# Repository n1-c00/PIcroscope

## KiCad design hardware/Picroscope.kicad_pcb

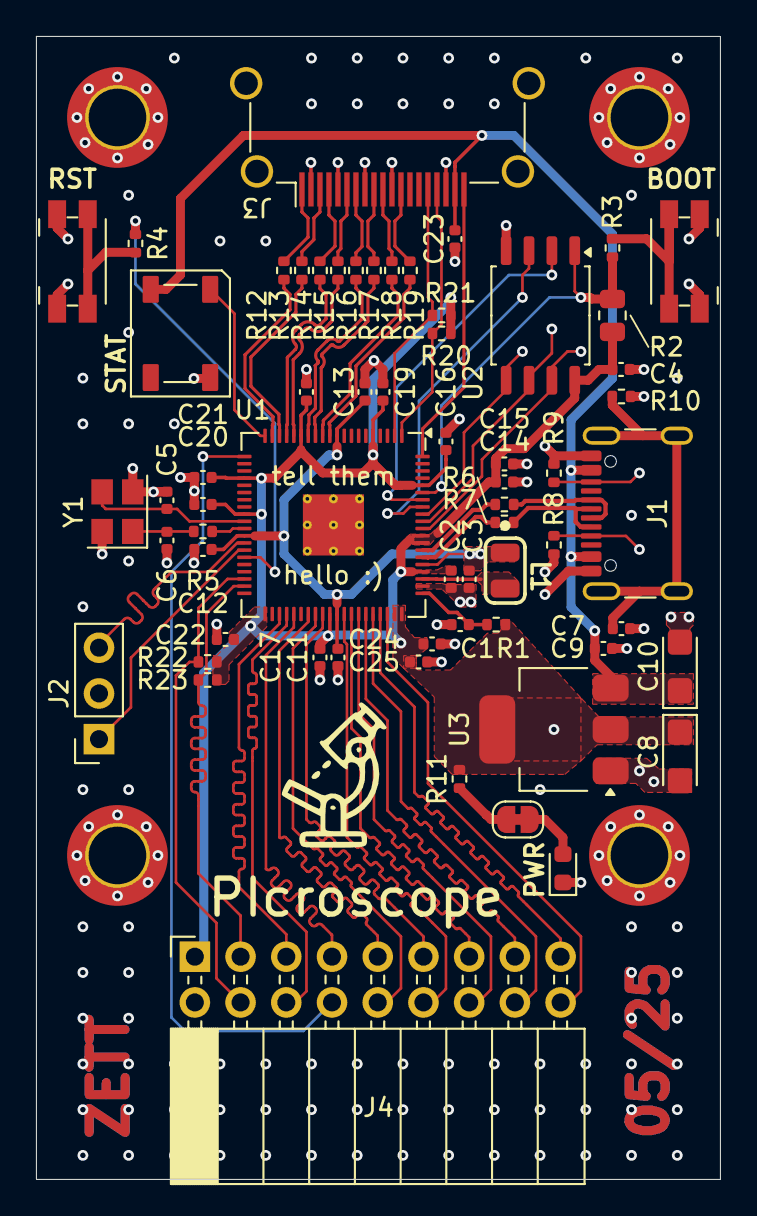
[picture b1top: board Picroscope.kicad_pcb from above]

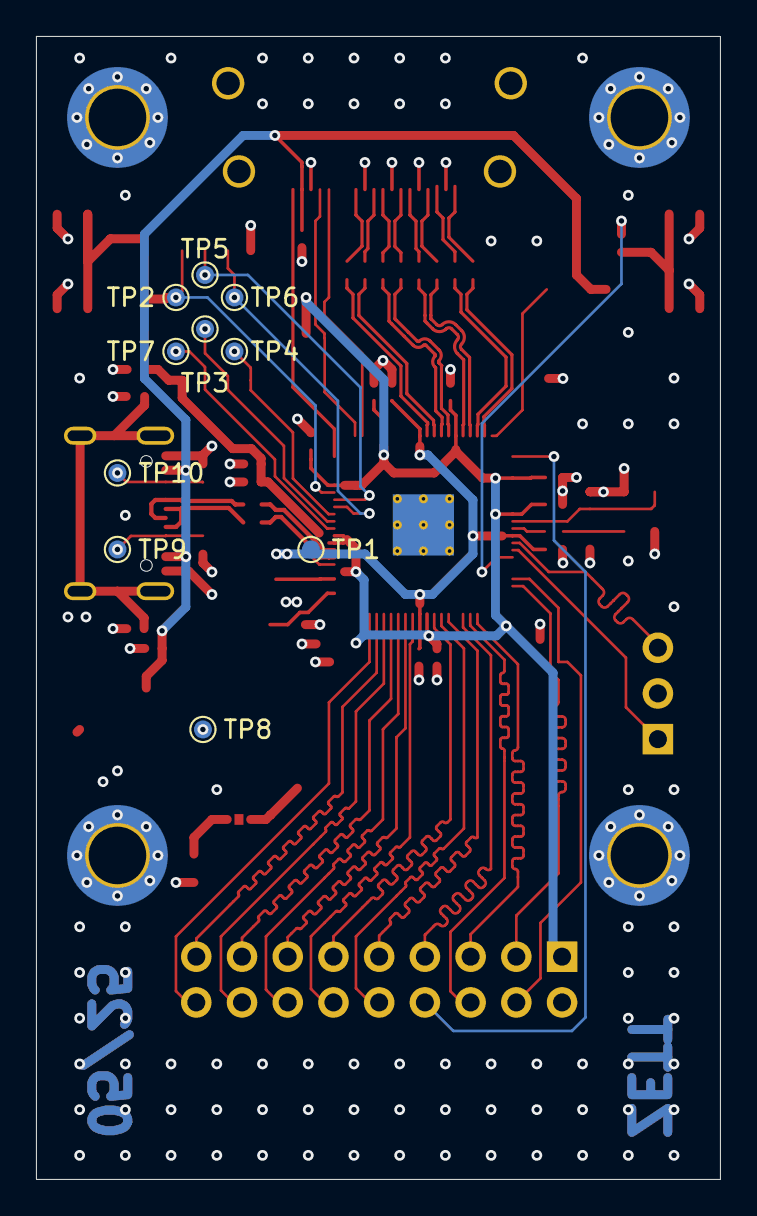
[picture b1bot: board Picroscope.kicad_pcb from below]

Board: 4 copper layers, 38.0 x 63.5 mm, 76 parts (10 on the bottom side), 65 nets.

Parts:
C1, C2, C3: 4.7u; C_0402_1005Metric
C4, C9, C11, C12, C13, C14, C15, C16, C17, C18, C19, C20, C21, C22, C23, C24, C25: 100n; C_0402_1005Metric
C5, C6: 15p; C_0402_1005Metric
C7: 100nF; C_0402_1005Metric
C8, C10: 22uF; CP_EIA-3216-18_Kemet-A
D1: LED; LED_0603_1608Metric
D2: WS2812B-2020; LED_WS2812B_PLCC4_5.0x5.0mm_P3.2mm
H1, H2, H3, H4: MountingHole_Pad; MountingHole_3.2mm_M3_DIN965_Pad_TopBottom
J1: USB_C_Receptacle_USB2.0_16P; USB_C_Receptacle_GCT_USB4105-xx-A_16P_TopMnt_Horizontal
J2: Conn_01x03_Pin; PinSocket_1x03_P2.54mm_Vertical
J3: HDMI_A; HDMI_A_Amphenol_10029449-x01xLF_Horizontal
J4: Conn_02x09_Odd_Even; PinSocket_2x09_P2.54mm_Horizontal
JP1: Jumper_2_Bridged; SolderJumper-2_P1.3mm_Bridged_RoundedPad1.0x1.5mm
L1: 3.3uH; RP235x_Inductor
R1, R6, R7: 27R; R_0402_1005Metric
R2: 1k; R_0805_2012Metric
R3, R4, R5, R11: 1k; R_0402_1005Metric
R8, R9, R10, R20, R21, R22, R23: 5.1k; R_0402_1005Metric
R12, R13, R14, R15, R16, R17, R18, R19: 270R; R_0402_1005Metric
SW1, SW2: SMD_Pushbutton; Panasonic_EVQPUJ_EVQPUA
TP1, TP2, TP3, TP4, TP5, TP6, TP7, TP8, TP9, TP10: TestPoint; TestPoint_Pad_D1.0mm
U1: RP2350B-QFN80; QFN-80-1EP_10x10mm_P0.4mm_EP3.4x3.4mm_ThermalVias
U2: W25Q32JVSS; SOIC-8_5.23x5.23mm_P1.27mm
U3: AMS1117-3.3; SOT-223-3_TabPin2
Y1: ABM8-272-T3; Crystal_SMD_3225-4Pin_3.2x2.5mm

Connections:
+1V1: C3.1, C11.1, C12.1, C13.1, L1.1, TP1.1, U1.10 (DVDD), U1.32 (DVDD), U1.51 (DVDD), U1.65 (VREG_FB)
+3V3: C2.1, C4.1, C8.1, C14.1, C15.1, C16.1, C17.1, C18.1, C19.1, C20.1, C21.1, C22.1, C24.1, C25.1, J4.1, R1.1, R2.1, R11.2, R20.1, R21.1, R22.1, R23.1, TP8.1, U1.5 (IOVDD), U1.15 (IOVDD), U1.24 (IOVDD), U1.29 (IOVDD), U1.41 (IOVDD), U1.50 (IOVDD), U1.59 (ADC_AVDD), U1.60 (IOVDD), U1.64 (VREG_VIN), U1.68 (USB_OTP_VDD), U1.69 (QSPI_IOVDD), U1.76 (IOVDD), U2.8 (VCC), U3.2 (VO)
/CAM_D2: J4.16, U1.56 (GPIO45_ADC5)
/CAM_D3: J4.15, U1.55 (GPIO44_ADC4)
/CAM_D4: J4.14, U1.54 (GPIO43_ADC3)
/CAM_D5: J4.13, U1.53 (GPIO42_ADC2)
/CAM_D6: J4.12, U1.52 (GPIO41_ADC1)
/CAM_D7: J4.11, U1.49 (GPIO40_ADC0)
/CAM_D8: J4.10, U1.48 (GPIO39)
/CAM_D9: J4.9, U1.47 (GPIO38)
/CAM_HSYNC: J4.6, U1.44 (GPIO35)
/CAM_PCLK: J4.7, U1.45 (GPIO36)
/CAM_PWDN: J4.18, U1.58 (GPIO47_ADC7)
/CAM_Reset: J4.17, U1.57 (GPIO46_ADC6)
/CAM_VSYNC: J4.5, U1.43 (GPIO34)
/CLKOUT0: J4.8, U1.21 (GPIO21)
/HDMI_CK+: J3.10 (CK+), R18.2
/HDMI_CK-: J3.12 (CK-), R19.2
/HDMI_D0+: J3.7 (D0+), R16.2
/HDMI_D0-: J3.9 (D0-), R17.2
/HDMI_D1+: J3.4 (D1+), R14.2
/HDMI_D1-: J3.6 (D1-), R15.2
/HDMI_D2+: J3.1 (D2+), R12.2
/HDMI_D2-: J3.3 (D2-), R13.2
/HDMI_HPD: J3.19 (HPD), U1.80 (GPIO3)
/I2C0_SCL: J3.15 (SCL), R21.2, U1.2 (GPIO5)
/I2C0_SDA: J3.16 (SDA), R20.2, U1.1 (GPIO4)
/I2C1_SCL: J4.3, R23.2, U1.39 (GPIO31)
/I2C1_SDA: J4.4, R22.2, U1.38 (GPIO30)
/MCU/Btn_BOOT: R3.2, SW1.2
/MCU/Btn_RUN: R4.1, SW2.2
/MCU/PUSB_D+: R6.1, U1.67 (USB_DP)
/MCU/PUSB_D-: R7.1, U1.66 (USB_DM)
/MCU/RUN: R4.2, U1.35 (RUN)
/MCU/SPI_CS: R2.2, R3.1, TP2.1, U1.75 (QSPI_SS), U2.1 (~CS)
/MCU/SPI_SCLK: TP3.1, U1.71 (QSPI_SCLK), U2.6 (CLK)
/MCU/SPI_SD0: TP4.1, U1.72 (QSPI_SD0), U2.5 (DI(IO0))
/MCU/SPI_SD1: TP5.1, U1.74 (QSPI_SD1), U2.2 (DO(IO1))
/MCU/SPI_SD2: TP6.1, U1.73 (QSPI_SD2), U2.3 (IO2)
/MCU/SPI_SD3: TP7.1, U1.70 (QSPI_SD3), U2.7 (IO3)
/MCU/SWDCLK: J2.3, U1.33 (SWCLK)
/MCU/SWDIO: J2.1, U1.34 (SWDIO)
/MCU/VREG_AVDD: C1.1, R1.2, U1.61 (VREG_AVDD)
/MCU/VREG_LX: L1.2, U1.63 (VREG_LX)
/MCU/Xin: C5.2, U1.30 (XIN), Y1.3
/MCU/Xout: R5.1, U1.31 (XOUT)
/MCU/Yout: C6.2, R5.2, Y1.1
/PDVI_CK+: R19.1, U1.11 (GPIO12)
/PDVI_CK-: R18.1, U1.12 (GPIO13)
/PDVI_D0+: R17.1, U1.13 (GPIO14)
/PDVI_D0-: R16.1, U1.14 (GPIO15)
/PDVI_D1+: R15.1, U1.16 (GPIO16)
/PDVI_D1-: R14.1, U1.17 (GPIO17)
/PDVI_D2+: R13.1, U1.18 (GPIO18)
/PDVI_D2-: R12.1, U1.19 (GPIO19)
/PWR_A: D1.2 (A), JP1.1 (A)
/STATUS_DIN: D2.3 (DIN), U1.20 (GPIO20)
/USB_CC1: J1.A5 (CC1), R8.2, TP9.1
/USB_CC2: J1.B5 (CC2), R9.2, TP10.1
/USB_D+: J1.A6 (D+), J1.B6 (D+), R6.2
/USB_D-: J1.A7 (D-), J1.B7 (D-), R7.2
/USB_SHIELD: C7.1, J1.S1 (SHIELD), R10.2
GND: C1.2, C2.2, C3.2, C4.2, C5.1, C6.1, C7.2, C8.2, C9.2, C10.2, C11.2, C12.2, C13.2, C14.2, C15.2, C16.2, C17.2, C18.2, C19.2, C20.2, C21.2, C22.2, C23.1, C24.2, C25.2, D1.1 (K), D2.2 (VSS), H1.1, H2.1, H3.1, H4.1, J1.A1 (GND), J1.A12 (GND), J1.B1 (GND), J1.B12 (GND), J2.2, J3.2 (D2S), J3.5 (D1S), J3.8 (D0S), J3.11 (CKS), J3.17 (GND), J3.SH, J4.2, R8.1, R9.1, R10.1, SW1.1, SW2.1, U1.62 (VREG_PGND), U1.81 (GND), U2.4 (GND), U3.1 (GND), Y1.2, Y1.4
unnamed: JP1.2 (B), R11.1
VBUS: C9.1, C10.1, C23.2, D2.4 (VDD), J1.A4 (VBUS), J1.A9 (VBUS), J1.B4 (VBUS), J1.B9 (VBUS), J3.18 (+5V), U3.3 (VI)

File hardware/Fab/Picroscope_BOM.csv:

"Id";"Designator";"Footprint";"Quantity";"Designation";"Supplier and ref";
1;"C24,C15,C22,C21,C25,C20,C13,C17,C19,C14,C4,C11,C16,C12,C23,C9,C18";"C_0402_1005Metric";17;"100n";;;
2;"C3,C1,C2";"C_0402_1005Metric";3;"4.7u";;;
3;"R15,R12,R19,R13,R18,R16,R17,R14";"R_0402_1005Metric";8;"270R";;;
4;"U1";"QFN-80-1EP_10x10mm_P0.4mm_EP3.4x3.4mm_ThermalVias";1;"RP2350B-QFN80";;;
5;"R1,R7,R6";"R_0402_1005Metric";3;"27R";;;
6;"U3";"SOT-223-3_TabPin2";1;"AMS1117-3.3";;;
7;"C10,C8";"C_0402_1005Metric";2;"4.7uF";;;
8;"U2";"SOIC-8_5.23x5.23mm_P1.27mm";1;"W25Q32JVSS";;;
9;"R9,R20,R23,R22,R8,R21";"R_0402_1005Metric";6;"5.1k";;;
10;"J4";"PinSocket_2x09_P2.54mm_Horizontal";1;"Conn_02x09_Odd_Even";;;
11;"C5,C6";"C_0402_1005Metric";2;"15p";;;
12;"J3";"HDMI_A_Amphenol_10029449-x01xLF_Horizontal";1;"HDMI_A";;;
13;"R4,R5,R11,R3";"R_0402_1005Metric";4;"1k";;;
14;"SW2,SW1";"Panasonic_EVQPUJ_EVQPUA";2;"SMD_Pushbutton";;;
15;"J1";"USB_C_Receptacle_GCT_USB4105-xx-A_16P_TopMnt_Horizontal";1;"USB_C_Receptacle_USB2.0_16P";;;
16;"D2";"LED_WS2812B_PLCC4_5.0x5.0mm_P3.2mm";1;"WS2812B-2020";;;
17;"L1";"RP235x_Inductor";1;"3.3uH";;;
18;"J2";"PinSocket_1x03_P2.54mm_Vertical";1;"Conn_01x03_Pin";;;
19;"D1";"LED_0603_1608Metric";1;"LED";;;
20;"Y1";"Crystal_SMD_3225-4Pin_3.2x2.5mm";1;"ABM8-272-T3";;;
21;"TP8,TP2,TP3,TP4,TP6,TP7,TP10,TP1,TP9,TP5";"TestPoint_Pad_D1.0mm";10;"TestPoint";;;

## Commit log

2025-03-28 added length tuning to 'crucial' traces except qspi
2025-05-03 final push for PCB V0.1
2025-05-05 changed C8 & C10 to tantalum caps
2025-05-05 added gitignore
2025-05-27 fixed short to GND on CLKOUT0
